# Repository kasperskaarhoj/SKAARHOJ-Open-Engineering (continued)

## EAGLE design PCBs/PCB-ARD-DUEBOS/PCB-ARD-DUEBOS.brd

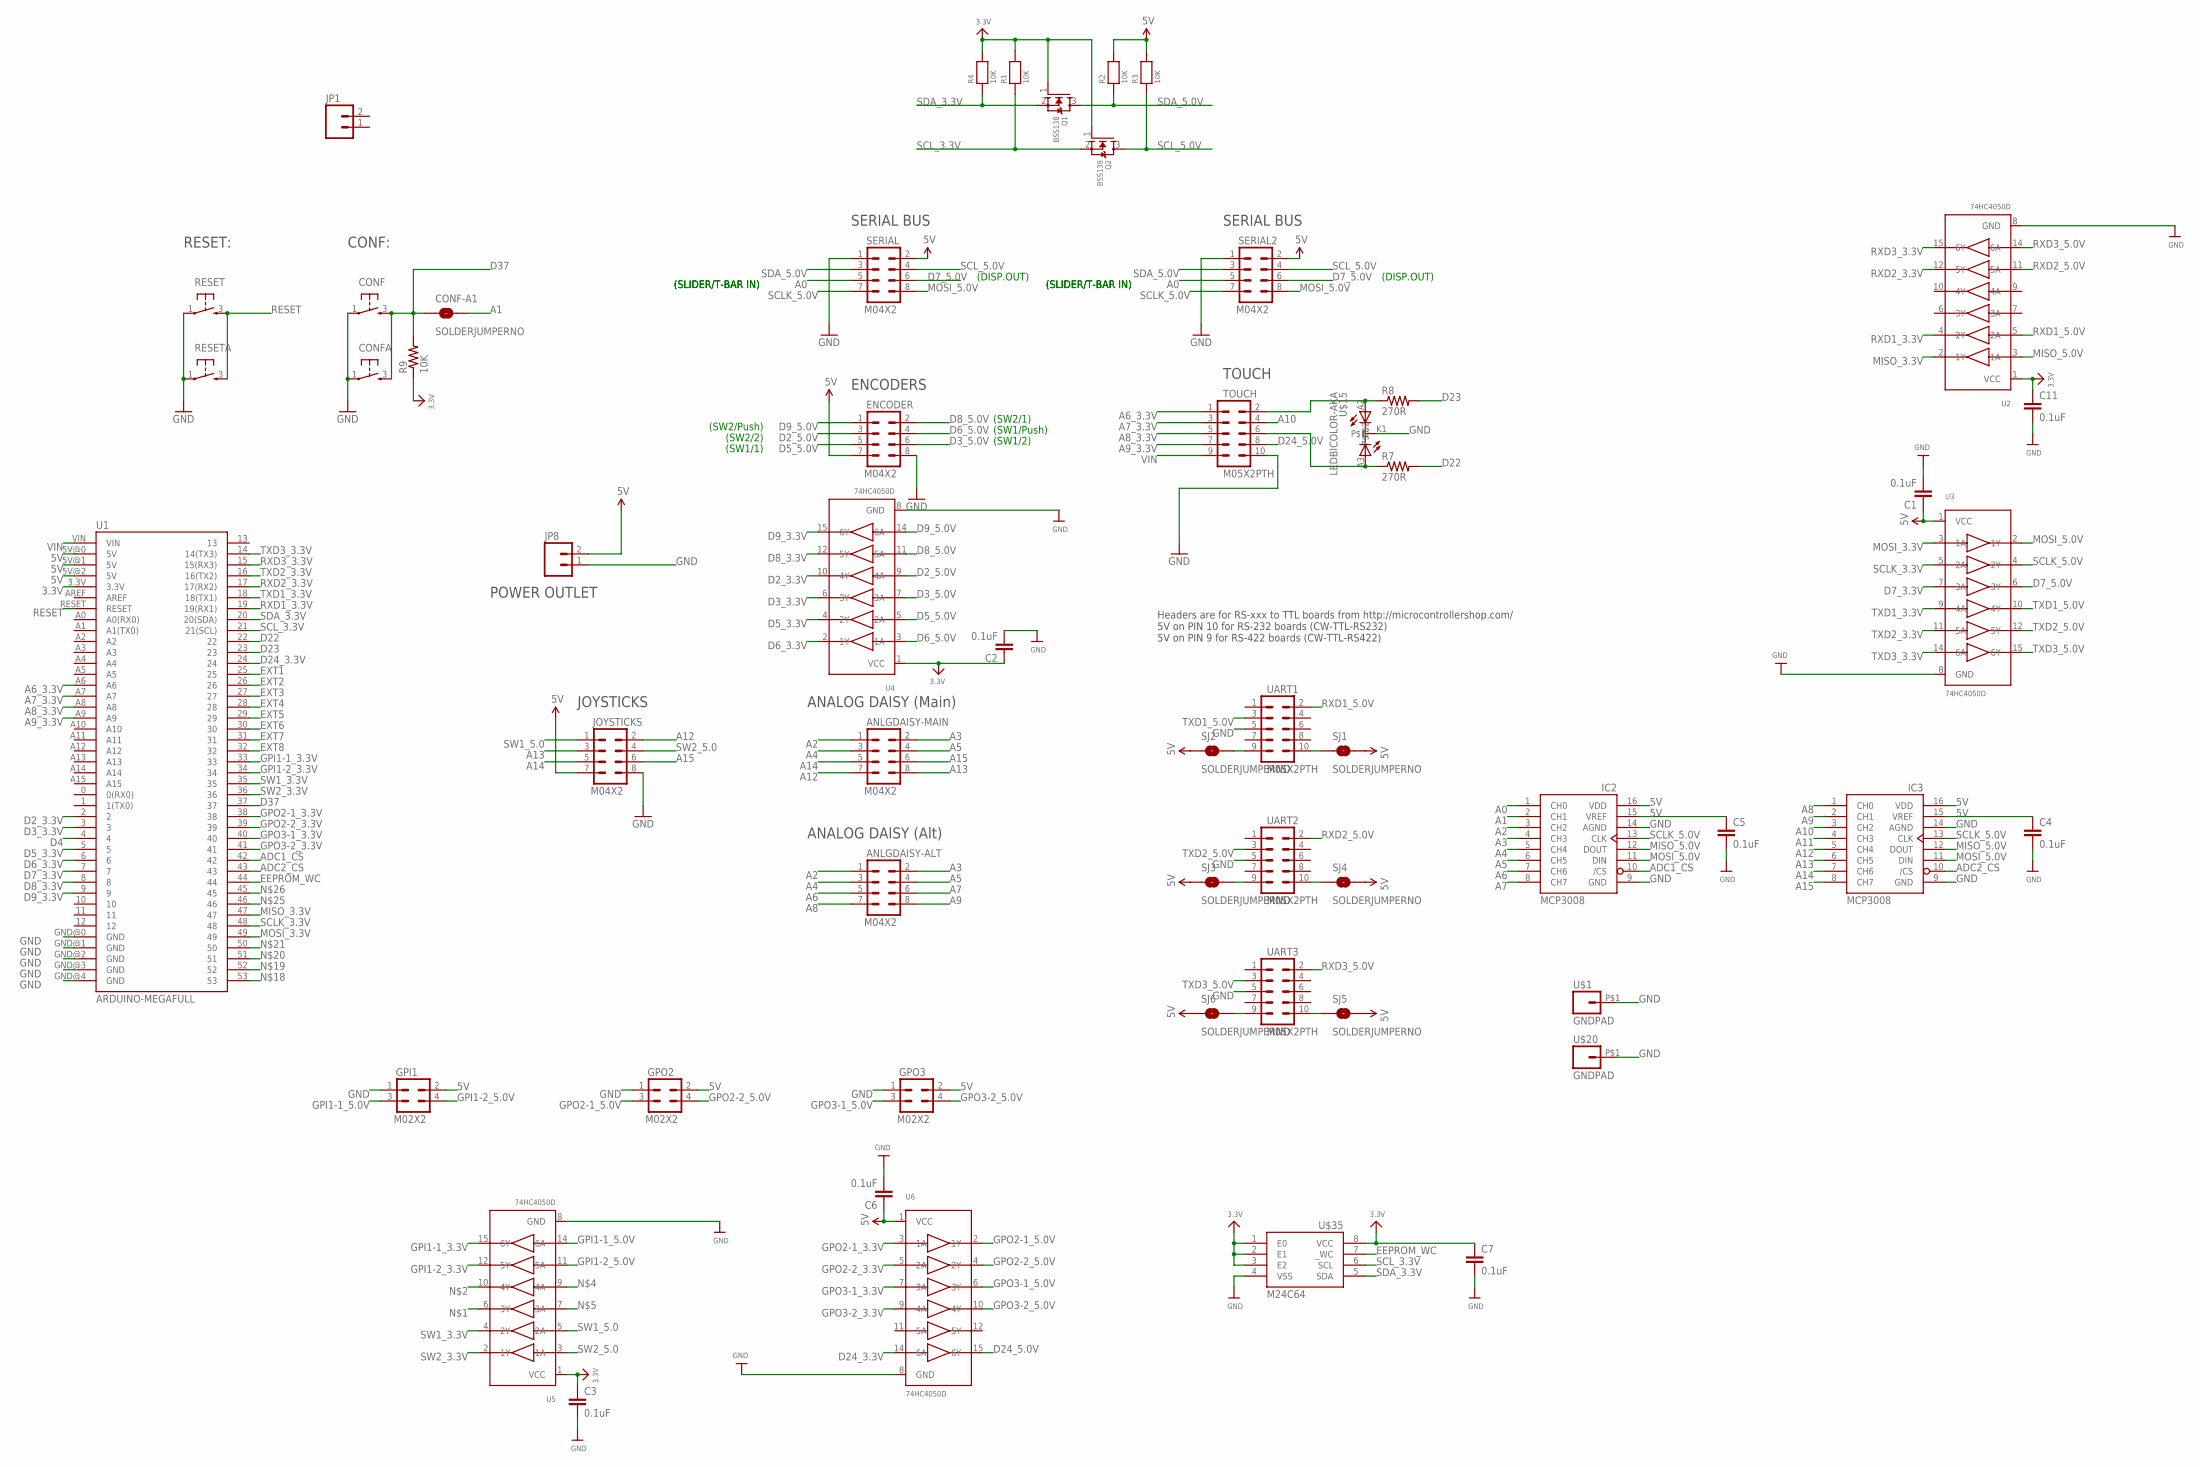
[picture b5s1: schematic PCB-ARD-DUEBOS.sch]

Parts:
ANLGDAISY-ALT: M04X2; 2X4
ANLGDAISY-MAIN: M04X2; 2X4
C1, C2, C3, C4, C5, C6, C7, C11: 0.1uF; 0603-CAP
CONF: TAC_SWITCH; PUSHBUTTON
CONF-A1: SOLDERJUMPERNO; SJ_2S-NO
CONFA: TAC_SWITCH; PUSHBUTTON
ENCODER: M04X2; 2X4
GPI1: M02X2; 2X2
GPO2, GPO3: M02X2; 2X2
IC2, IC3: MCP3008SOIC; SOIC16
JOYSTICKS: M04X2; 2X4
JP1: M02PTH; 1X02
JP8: M02PTH4; 1X02_XTRA_BIG
Q1, Q2: BSS138; SOT23-WIDE
R1, R2, R3, R4: 10K; 0805
R7, R8: 270R; 0603-RES
R9: 10K; 0603-RES
RESET: TAC_SWITCH; PUSHBUTTON
RESETA: TAC_SWITCH; PUSHBUTTON
SERIAL, SERIAL2: M04X2; 2X4
SJ1, SJ2, SJ3, SJ4, SJ5, SJ6: SOLDERJUMPERNO; SJ_2S-NO
TOUCH: M05X2PTH; AVR_ICSP
U1: ARDUINO-MEGAFULL; ARDUINO_MEGA
U2, U3, U4, U5, U6: 74HC4050D; TSSOP16
U$1, U$20: GNDPAD; 3.2MMPAD
U$15: LEDBICOLOR-AKA; LED5MM-BICOLOR
U$35: M24C64; TSSOP8
UART1, UART2, UART3: M05X2PTH; AVR_ICSP

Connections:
3.3V: C2.1, C3.1, C7.1, C11.1, Q1.1 (G), Q2.1 (G), R1.2, R4.2, R9.1, U1.3.3V, U2.1 (VCC), U4.1 (VCC), U5.1 (VCC), U$35.1 (E0), U$35.2 (E1), U$35.3 (E2), U$35.8 (VCC)
5V: C1.1, C4.1, C5.1, C6.1, ENCODER.7, GPI1.2, GPO2.2, GPO3.2, IC2.15 (VREF), IC2.16 (VDD), IC3.15 (VREF), IC3.16 (VDD), JOYSTICKS.7, JP8.2, R2.2, R3.2, SERIAL.2, SERIAL2.2, SJ1.2, SJ2.1, SJ3.1, SJ4.2, SJ5.2, SJ6.1, U1.5V@0 (5V), U1.5V@1 (5V), U1.5V@2 (5V), U3.1 (VCC), U6.1 (VCC)
A0: IC2.1 (CH0), SERIAL.5, SERIAL2.5
A1: CONF-A1.2, IC2.2 (CH1)
A2: ANLGDAISY-ALT.1, ANLGDAISY-MAIN.1, IC2.3 (CH2)
A3: ANLGDAISY-ALT.2, ANLGDAISY-MAIN.2, IC2.4 (CH3)
A4: ANLGDAISY-ALT.3, ANLGDAISY-MAIN.3, IC2.5 (CH4)
A5: ANLGDAISY-ALT.4, ANLGDAISY-MAIN.4, IC2.6 (CH5)
A6: ANLGDAISY-ALT.5, IC2.7 (CH6)
A6_3.3V: TOUCH.1, U1.A6
A7: ANLGDAISY-ALT.6, IC2.8 (CH7)
A7_3.3V: TOUCH.3, U1.A7
A8: ANLGDAISY-ALT.7, IC3.1 (CH0)
A8_3.3V: TOUCH.5, U1.A8
A9: ANLGDAISY-ALT.8, IC3.2 (CH1)
A9_3.3V: TOUCH.7, U1.A9
A10: IC3.3 (CH2), TOUCH.4
A11: IC3.4 (CH3)
A12: ANLGDAISY-MAIN.7, IC3.5 (CH4), JOYSTICKS.2
A13: ANLGDAISY-MAIN.8, IC3.6 (CH5), JOYSTICKS.3
A14: ANLGDAISY-MAIN.5, IC3.7 (CH6), JOYSTICKS.5
A15: ANLGDAISY-MAIN.6, IC3.8 (CH7), JOYSTICKS.6
ADC1_CS: IC2.10 (/CS), U1.42
ADC2_CS: IC3.10 (/CS), U1.43
D2_3.3V: U1.2, U4.10 (4Y)
D2_5.0V: ENCODER.3, U4.9 (4A)
D3_3.3V: U1.3, U4.6 (3Y)
D3_5.0V: ENCODER.6, U4.7 (3A)
D4: U1.4
D5_3.3V: U1.5, U4.4 (2Y)
D5_5.0V: ENCODER.5, U4.5 (2A)
D6_3.3V: U1.6, U4.2 (1Y)
D6_5.0V: ENCODER.4, U4.3 (1A)
D7_3.3V: U1.7, U3.7 (3A)
D7_5.0V: SERIAL.6, SERIAL2.6, U3.6 (3Y)
D8_3.3V: U1.8, U4.12 (5Y)
D8_5.0V: ENCODER.2, U4.11 (5A)
D9_3.3V: U1.9, U4.15 (6Y)
D9_5.0V: ENCODER.1, U4.14 (6A)
D22: R7.2, U1.22
D23: R8.2, U1.23
D24_3.3V: U1.24, U6.14 (6A)
D24_5.0V: TOUCH.8, U6.15 (6Y)
D37: CONF.3, CONF-A1.1, CONFA.3, R9.2, U1.37
EEPROM_WC: U1.44, U$35.7 (_WC)
EXT1: U1.25
EXT2: U1.26
EXT3: U1.27
EXT4: U1.28
EXT5: U1.29
EXT6: U1.30
EXT7: U1.31
EXT8: U1.32
GND: C1.2, C2.2, C3.2, C4.2, C5.2, C6.2, C7.2, C11.2, CONF.1, CONFA.1, ENCODER.8, GPI1.1, GPO2.1, GPO3.1, IC2.9 (GND), IC2.14 (AGND), IC3.9 (GND), IC3.14 (AGND), JOYSTICKS.8, JP8.1, RESET.1, RESETA.1, SERIAL.1, SERIAL2.1, TOUCH.10, U1.GND@0 (GND), U1.GND@1 (GND), U1.GND@2 (GND), U1.GND@3 (GND), U1.GND@4 (GND), U2.8 (GND), U3.8 (GND), U4.8 (GND), U5.8 (GND), U6.8 (GND), U$1.P$1, U$15.K1, U$20.P$1, U$35.4 (VSS), UART1.5, UART2.5, UART3.5
GPI1-1_3.3V: U1.33, U5.15 (6Y)
GPI1-1_5.0V: GPI1.3, U5.14 (6A)
GPI1-2_3.3V: U1.34, U5.12 (5Y)
GPI1-2_5.0V: GPI1.4, U5.11 (5A)
GPO2-1_3.3V: U1.38, U6.3 (1A)
GPO2-1_5.0V: GPO2.3, U6.2 (1Y)
GPO2-2_3.3V: U1.39, U6.5 (2A)
GPO2-2_5.0V: GPO2.4, U6.4 (2Y)
GPO3-1_3.3V: U1.40, U6.7 (3A)
GPO3-1_5.0V: GPO3.3, U6.6 (3Y)
GPO3-2_3.3V: U1.41, U6.9 (4A)
GPO3-2_5.0V: GPO3.4, U6.10 (4Y)
MISO_3.3V: U1.47, U2.2 (1Y)
MISO_5.0V: IC2.12 (DOUT), IC3.12 (DOUT), U2.3 (1A)
MOSI_3.3V: U1.49, U3.3 (1A)
MOSI_5.0V: IC2.11 (DIN), IC3.11 (DIN), SERIAL.8, SERIAL2.8, U3.2 (1Y)
unnamed: SJ6.2, UART3.9
unnamed: SJ3.2, UART2.9
unnamed: SJ2.2, UART1.9
unnamed: SJ1.1, UART1.10
unnamed: SJ4.1, UART2.10
unnamed: SJ5.1, UART3.10
unnamed: R8.1, TOUCH.2, U$15.A2
unnamed: R7.1, TOUCH.6, U$15.A3
RESET: RESET.3, RESETA.3, U1.RESET
RXD1_3.3V: U1.19 (19(RX1)), U2.4 (2Y)
RXD1_5.0V: U2.5 (2A), UART1.2
RXD2_3.3V: U1.17 (17(RX2)), U2.12 (5Y)
RXD2_5.0V: U2.11 (5A), UART2.2
RXD3_3.3V: U1.15 (15(RX3)), U2.15 (6Y)
RXD3_5.0V: U2.14 (6A), UART3.2
SCLK_3.3V: U1.48, U3.5 (2A)
SCLK_5.0V: IC2.13 (CLK), IC3.13 (CLK), SERIAL.7, SERIAL2.7, U3.4 (2Y)
SCL_3.3V: Q2.2 (S), R1.1, U1.21 (21(SCL)), U$35.6 (SCL)
SCL_5.0V: Q2.3 (D), R3.1, SERIAL.4, SERIAL2.4
SDA_3.3V: Q1.2 (S), R4.1, U1.20 (20(SDA)), U$35.5 (SDA)
SDA_5.0V: Q1.3 (D), R2.1, SERIAL.3, SERIAL2.3
SW1_3.3V: U1.35, U5.4 (2Y)
SW1_5.0: JOYSTICKS.1, U5.5 (2A)
SW2_3.3V: U1.36, U5.2 (1Y)
SW2_5.0: JOYSTICKS.4, U5.3 (1A)
TXD1_3.3V: U1.18 (18(TX1)), U3.9 (4A)
TXD1_5.0V: U3.10 (4Y), UART1.3
TXD2_3.3V: U1.16 (16(TX2)), U3.11 (5A)
TXD2_5.0V: U3.12 (5Y), UART2.3
TXD3_3.3V: U1.14 (14(TX3)), U3.14 (6A)
TXD3_5.0V: U3.15 (6Y), UART3.3
VIN: TOUCH.9, U1.VIN

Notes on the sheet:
JOYSTICKS
Headers are for RS-xxx to TTL boards from http://microcontrollershop.com/ 5V on PIN 10 for RS-232 boards (CW-TTL-RS232) 5V on PIN 9 for RS-422 boards (CW-TTL-RS422)
ENCODERS
SERIAL BUS
TOUCH
(SLIDER/T-BAR IN)
(SW2/Push)
(SW2/2)
(SW1/1)
(SW2/1)
(SW1/Push)
(SW1/2)
(DISP.OUT)
RESET:
CONF:
ANALOG DAISY (Main)
ANALOG DAISY (Alt)
POWER OUTLET

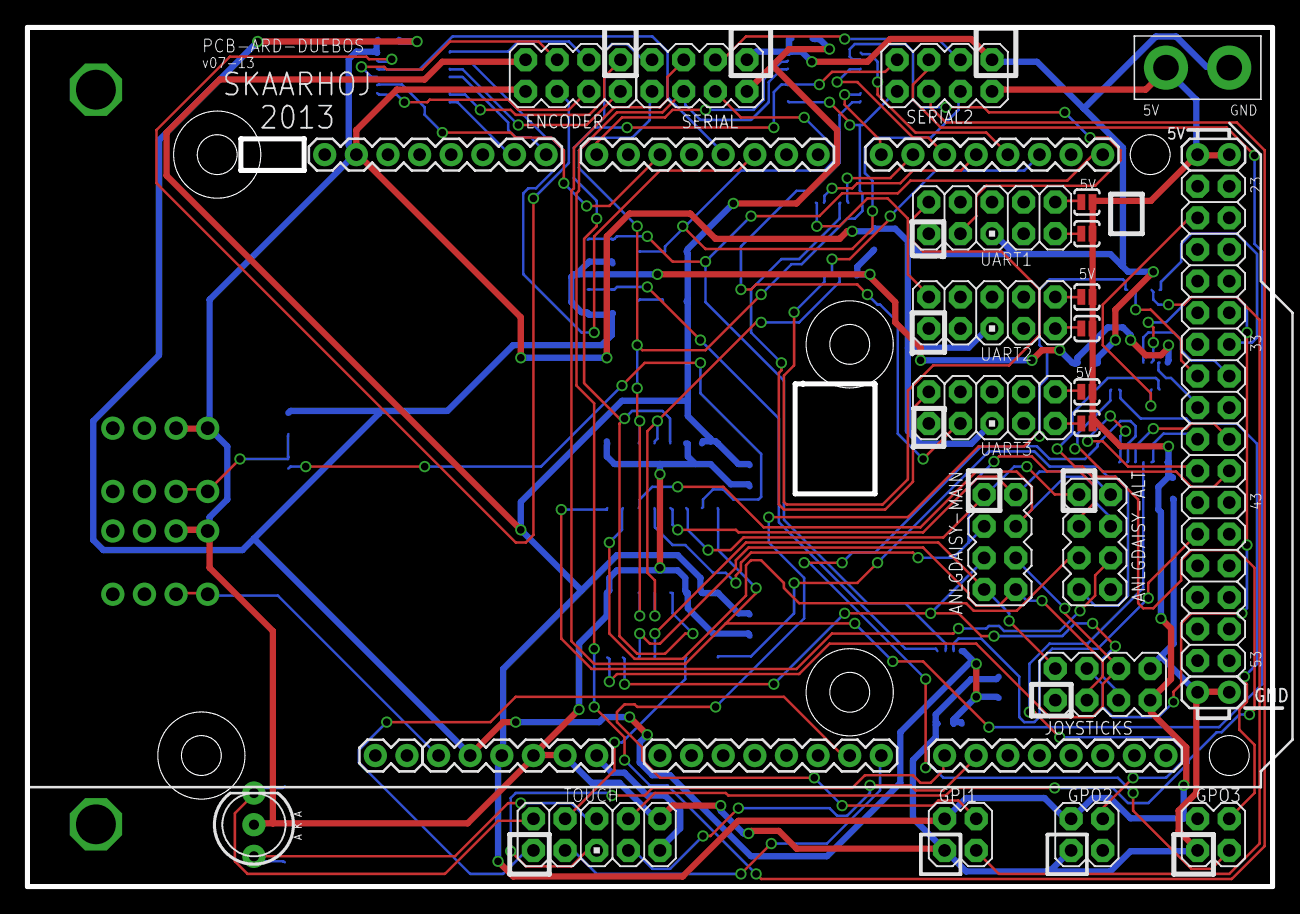
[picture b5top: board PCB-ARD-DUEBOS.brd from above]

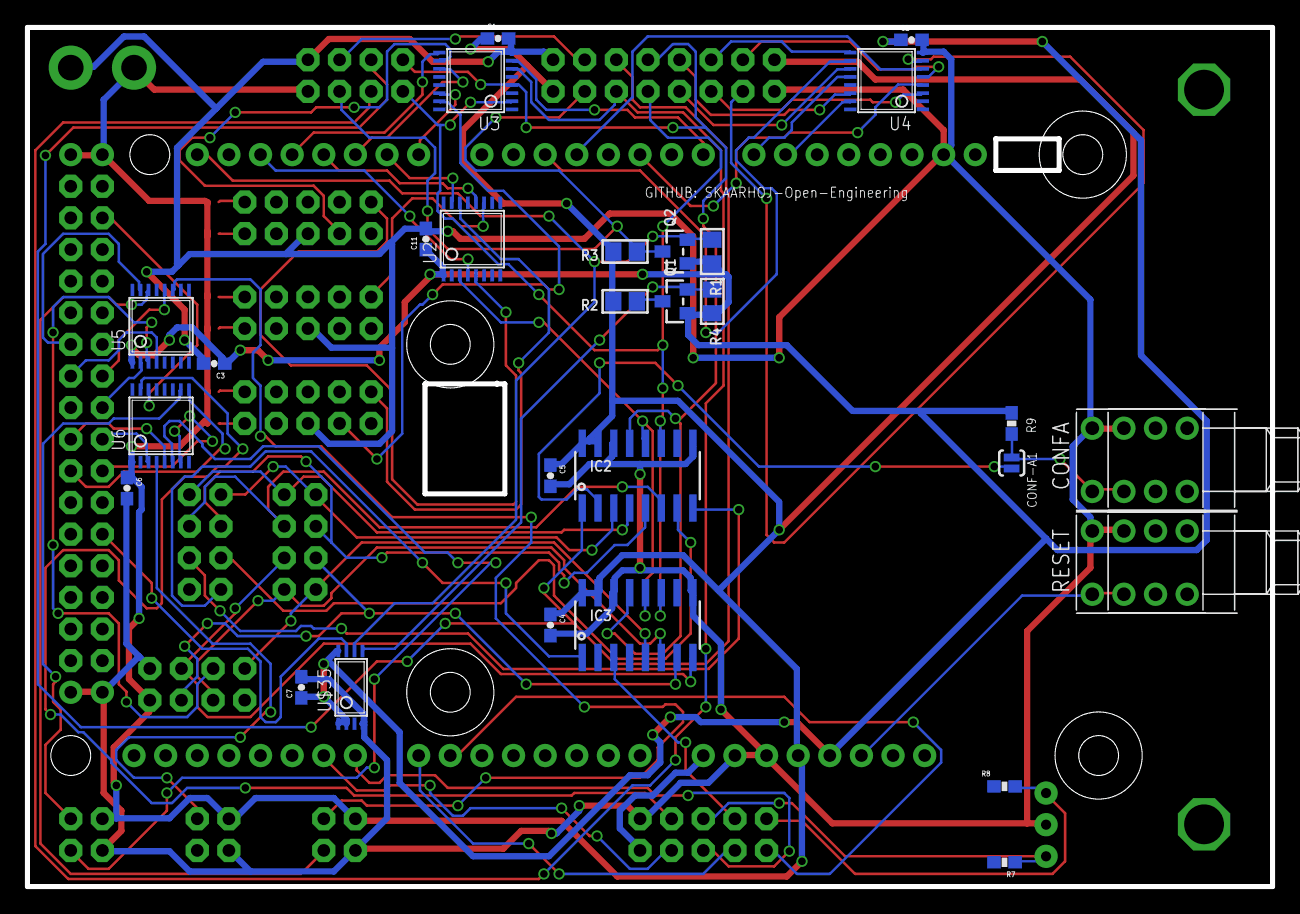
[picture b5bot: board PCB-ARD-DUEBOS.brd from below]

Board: 2 copper layers, 100.0 x 69.0 mm, 55 parts (30 on the bottom side), 92 nets.
